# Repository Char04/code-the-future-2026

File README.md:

# Code the Future 2026

# Comunicare Drona-Turn de Control - VirtualBB Hackathon Siemens 2026

A project that simulates the communication between a drone and a control tower/station. In this project we're using an ESP32 to simulate the internal computer of a drone that connects and sends real-time data to a Raspberry Pi which acts as the control tower.

## Main Features
* A visual interface built in Python (Tkinter) on a Raspberry Pi that displays in real-time the data that are transmitted from the ESP32 board.
* A settings module that allows applying offsets to received sensor values in order to test the drone's safety warnings. You can change the following:
  * Altitude - altering reference value and warning threshold
  * Atmospheric Pressure - altering reference threshold
  * Chip Temperature - altering reference threshold
  * Humidity - altering reference threshold
  * Gas/Analog sensor values - altering the reference data to test the shortcircuit checking warning.
  * A reset button to revert to the normal values transmitted from the ESP32 board.
* Safety and Alert System: Visual warnings and pop-ups for weather conditions and short-circuits.

## Hardware Architecture (The Breadboard Digital Twin)
The system is powered by an ESP32, which collects data from the following modules:
* MPU6050: Gyroscope and Accelerometer for determining orientation and acceleration.
* BMP280: Barometric pressure, altitude, and chip temperature sensor.
* DHT22: Sensor for external temperature and humidity.
* Gas / Analog Sensor: Detects high spikes in board's surrounding air and flags them as short-circuits.

The hardware design was upgraded from a basic breadboard prototype to a PCB designed in KiCad, featuring optimized routing and safety components.

## Software Architecture (The Drone Digital Twin)
The data is received and processed by a Python script running on the Raspberry Pi (Control Tower). 
The interface uses canvas graphics to simulate an artificial horizon and allows the user to monitor safety limits, including maximum altitude, low pressure thresholds, wet condition risks, and hardware overheating.

## Setup / How to run

### 1. Drone Component (ESP32)
The code inside 'src/main.cpp' is meant to be compiled and uploaded using the Arduino IDE (or the PlatformIO extension).

Make sure you install the following libraries before uploading:
* PubSubClient
* Adafruit MPU6050
* Adafruit BMP280 Library
* DHT sensor library

Update the ssid, password, and mqtt_server variables in the code with your local network credentials.

If you use VS Code with Platformio Extension add the header #include <Arduino.h>.
If you use Arduino IDE save the ESP32 file as .ino.

Make sure you connected the pins as they should!

### 2. Control Tower Component (Dashboard / Monitoring)
The code inside 'dashboard/live_dashboard.py' is a Python script meant to run on the Raspberry Pi (or any PC connected to the same network) to monitor and process the data sent by the ESP32 via MQTT.

Make sure you install the following library before running:

```bash
pip install paho-mqtt

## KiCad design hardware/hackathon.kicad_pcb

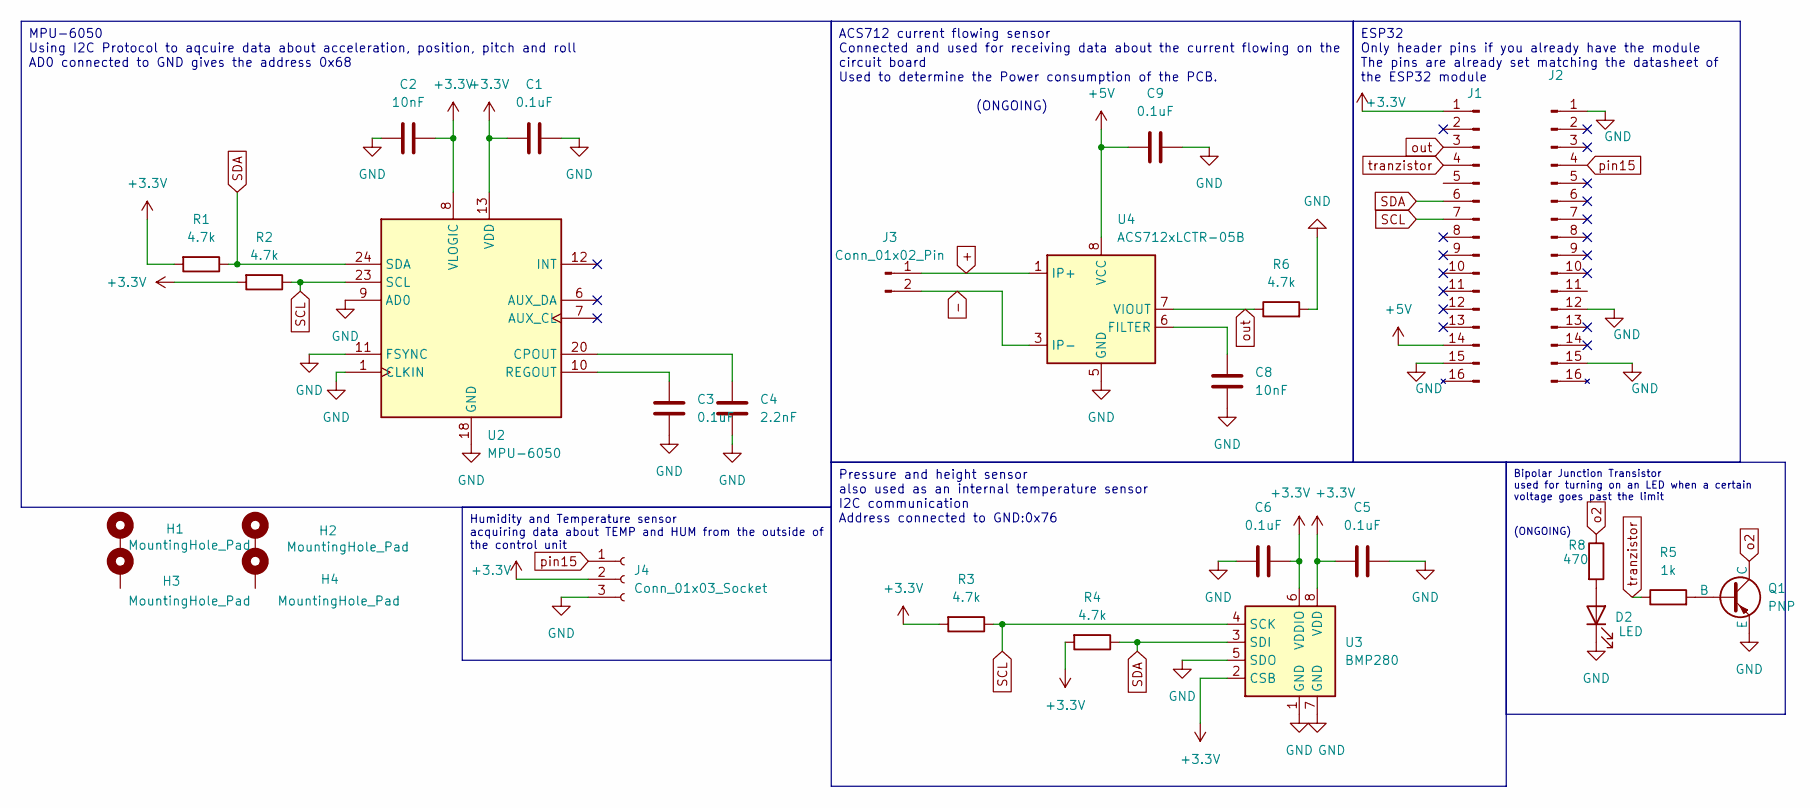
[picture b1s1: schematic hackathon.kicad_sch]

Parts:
C1, C3, C5, C6, C9: 0.1uF; C_0603_1608Metric
C2, C8: 10nF; C_0603_1608Metric
C4: 2.2nF; C_0603_1608Metric
D2: LED; LED_0603_1608Metric
H1, H2, H3, H4: MountingHole_Pad; MountingHole_2.2mm_M2_Pad_Via
J1, J2: Conn_01x16_Pin; PinHeader_1x16_P2.54mm_Vertical
J3: Conn_01x02_Pin; PinSocket_1x02_P2.54mm_Vertical
J4: Conn_01x03_Socket; PinHeader_1x03_P2.54mm_Vertical
Q1: PNP; TO-92_Inline
R1, R2, R3, R4, R6: 4.7k; R_0603_1608Metric
R5: 1k; R_0603_1608Metric
R8: 470; R_0603_1608Metric
U2: MPU-6050; InvenSense_QFN-24_4x4mm_P0.5mm
U3: BMP280; Bosch_LGA-8_2x2.5mm_P0.65mm_ClockwisePinNumbering
U4: ACS712xLCTR-05B; SOIC-8_3.9x4.9mm_P1.27mm

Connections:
+: J3.1, U4.1 (IP+), U4.2 (IP+)
+3.3V: C1.2, C2.2, C5.2, C6.1, J1.1, J4.2, R1.2, R2.2, R3.2, R4.2, U2.8 (VLOGIC), U2.13 (VDD), U3.2 (CSB), U3.6 (VDDIO), U3.8 (VDD)
+5V: C9.1, J1.14, U4.8 (VCC)
-: J3.2, U4.3 (IP-), U4.4 (IP-)
GND: C1.1, C2.1, C3.1, C4.2, C5.1, C6.2, C8.2, C9.2, D2.1 (K), J1.15, J2.1, J2.12, J2.15, J4.3, Q1.3 (E), R6.2, U2.1 (CLKIN), U2.9 (AD0), U2.11 (FSYNC), U2.18 (GND), U3.1 (GND), U3.5 (SDO), U3.7 (GND), U4.5 (GND)
unnamed: D2.2 (A), R8.2
unnamed: Q1.2 (B), R5.2
unnamed: C4.1, U2.20 (CPOUT)
unnamed: C3.2, U2.10 (REGOUT)
unnamed: C8.1, U4.6 (FILTER)
SCL: J1.7, R2.1, R3.1, U2.23 (SCL), U3.4 (SCK)
SDA: J1.6, R1.1, R4.1, U2.24 (SDA), U3.3 (SDI)
o2: Q1.1 (C), R8.1
out: J1.3, R6.1, U4.7 (VIOUT)
pin15: J2.4, J4.1
tranzistor: J1.4, R5.1

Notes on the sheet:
Pressure and height sensor also used as an internal temperature sensor I2C communication Address connected to GND:0x76
Bipolar Junction Transistor used for turning on an LED when a certain voltage goes past the limit (ONGOING)
ESP32 Only header pins if you already have the module The pins are already set matching the datasheet of the ESP32 module
Humidity and Temperature sensor acquiring data about TEMP and HUM from the outside of the control unit
MPU-6050 Using I2C Protocol to aqcuire data about acceleration, position, pitch and roll AD0 connected to GND gives the address 0x68
ACS712 current flowing sensor Connected and used for receiving data about the current flowing on the circuit board Used to determine the Power consumption of the PCB. (ONGOING)

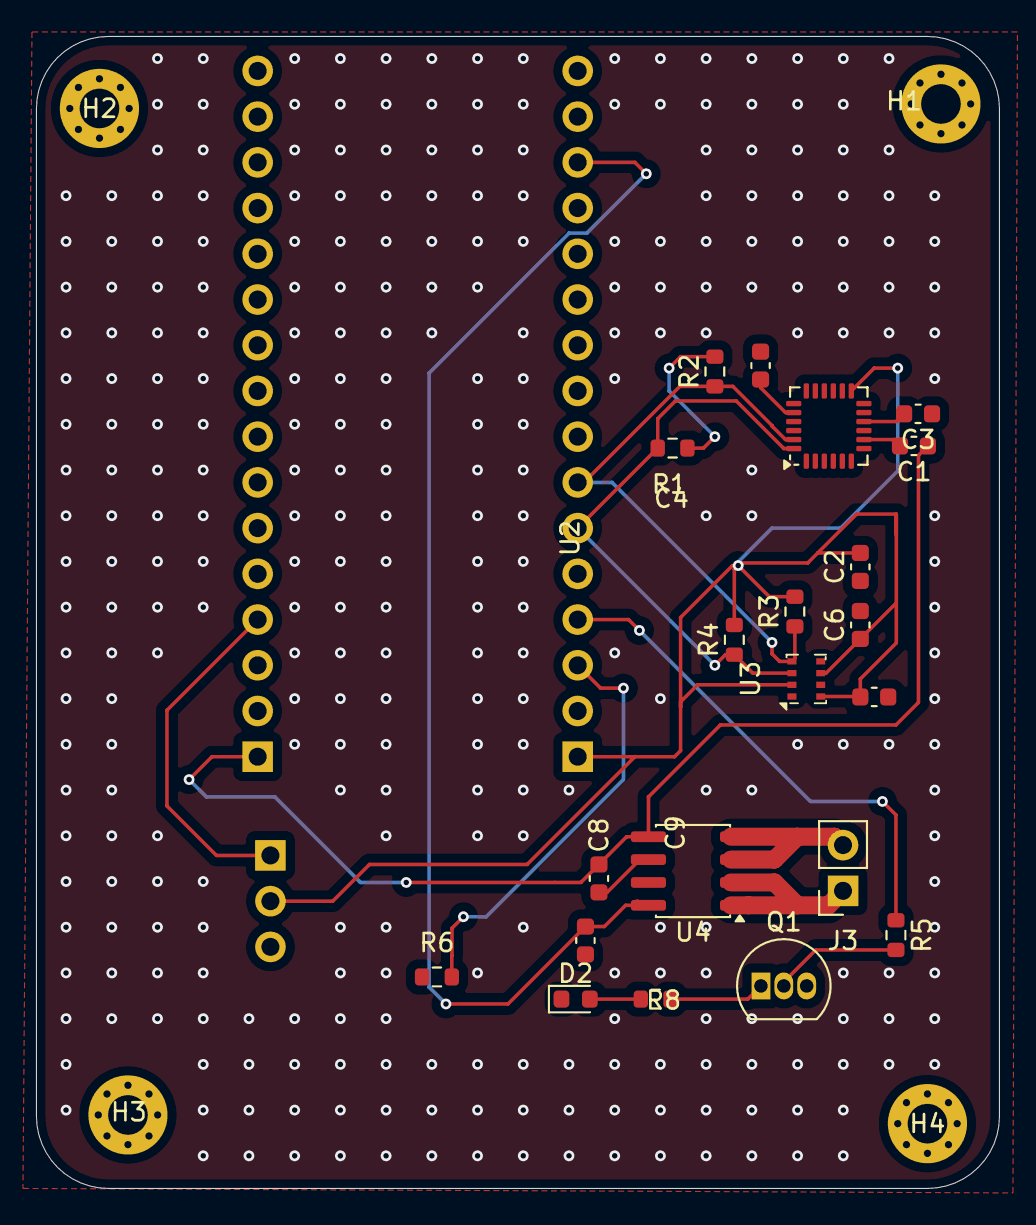
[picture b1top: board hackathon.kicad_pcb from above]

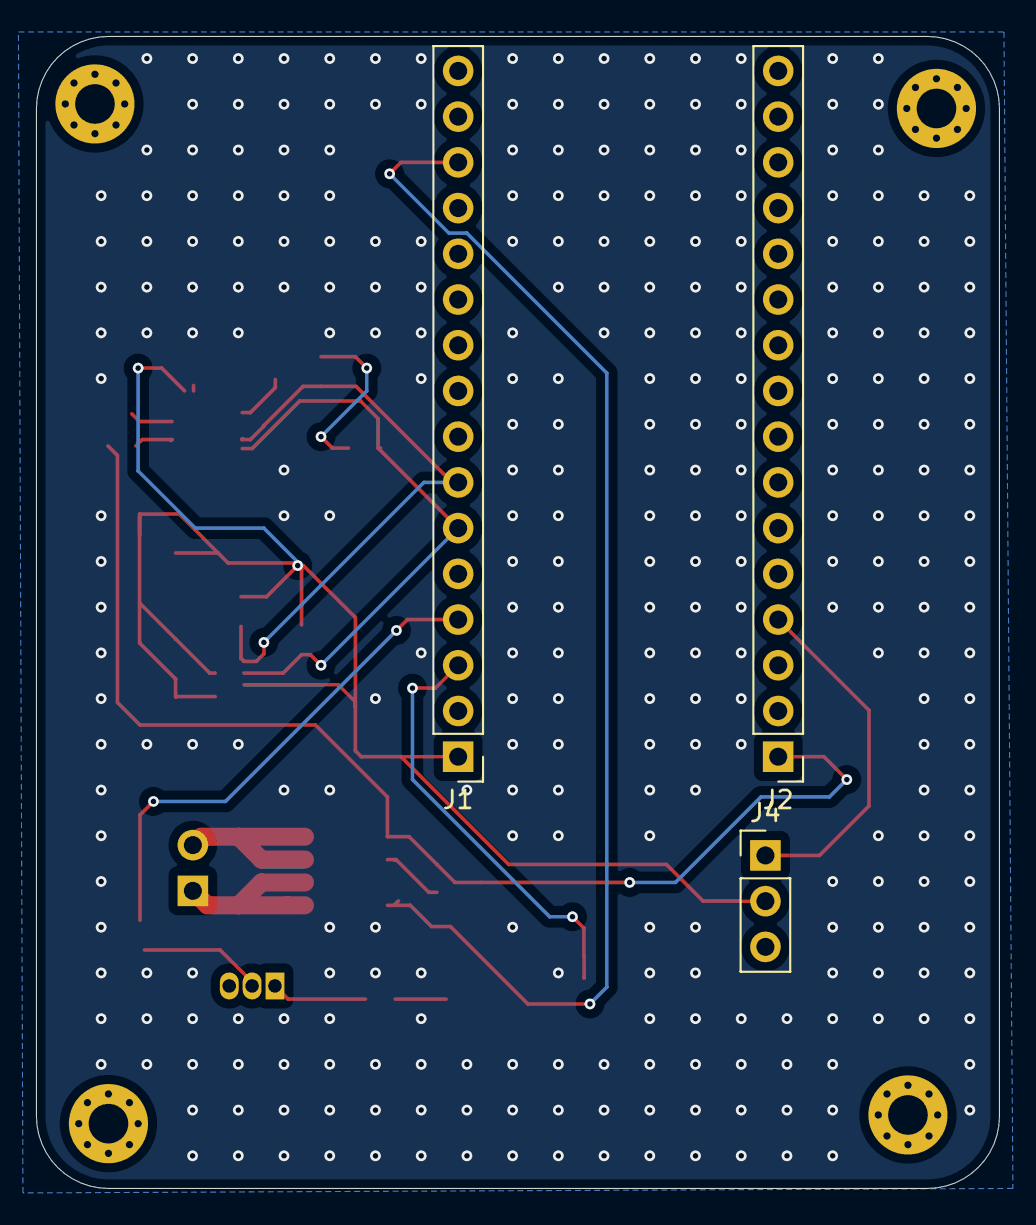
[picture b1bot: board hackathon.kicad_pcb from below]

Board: 2 copper layers, 53.5 x 64.0 mm, 28 parts (3 on the bottom side), 16 nets.

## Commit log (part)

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2026-04-23 Add ESP32 main code
2026-04-23 Add MQTT dashboard tools and update README instructions
2026-04-24 Add BMP280 sensor and update HUD telemetry
2026-04-24 Add DHT22 and MQ3 gas sensor
2026-04-24 Add altitude tape, fix axis mirroring and enhance visual layout
2026-04-24 Implement DHT22 data acquisition with 2 sec interval logic
2026-04-24 Improve dashboard with altitude alerts and simulated offset capabilities
2026-04-24 Speed and sensor last improvements
2026-04-24 Add gas simulation with pop-up alert, reset button and clean up UI code
2026-04-24 Overhaul dashboard with transparent full-screen HUD and advanced simulation
2026-04-24 Add raw KiCad PCB design files
2026-04-24 Update README.md and add presentation
